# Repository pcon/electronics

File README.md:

# Electronics Projects

This is a home for my various electronic projects.

# Home Monitor
This board is designed to take a WeMos D1 mini and provide traces to a OLED display and a humidity / temperature sensor.

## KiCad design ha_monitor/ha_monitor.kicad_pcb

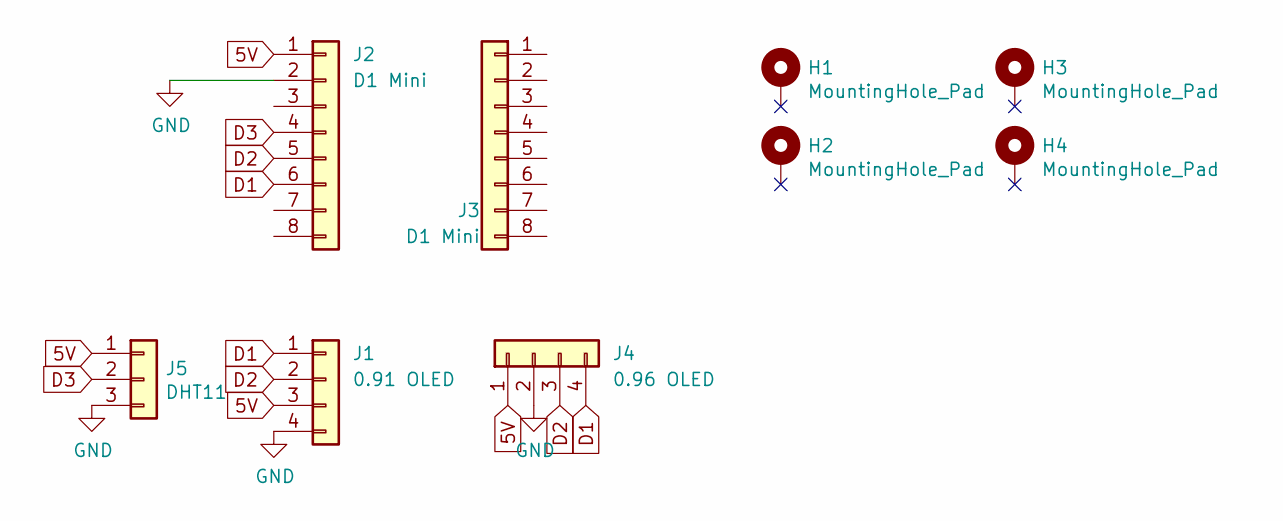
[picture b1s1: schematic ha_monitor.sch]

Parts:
H1, H2, H3, H4: MountingHole_Pad; MountingHole_3.2mm_M3_Pad
J1: 0.91 OLED; PinSocket_1x04_P2.54mm_Vertical
J2, J3: D1 Mini; PinSocket_1x08_P2.54mm_Vertical
J4: 0.96 OLED; PinSocket_1x04_P2.54mm_Vertical
J5: DHT11; PinSocket_1x03_P2.54mm_Vertical

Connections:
5V: J1.3, J2.1, J4.1, J5.1
D1: J1.1, J2.6, J4.4
D2: J1.2, J2.5, J4.3
D3: J2.4, J5.2
GND: J1.4, J2.2, J4.2, J5.3

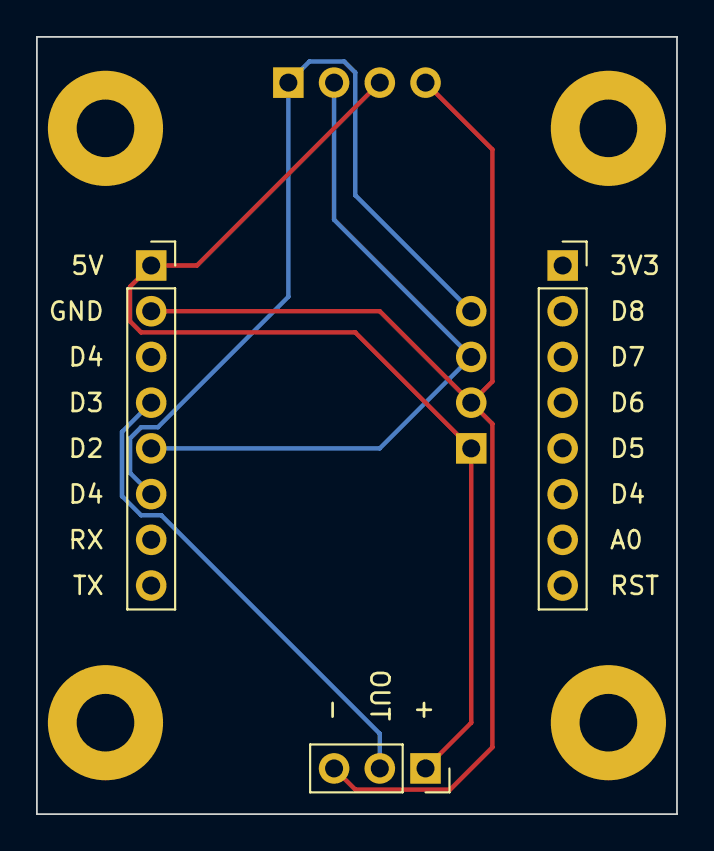
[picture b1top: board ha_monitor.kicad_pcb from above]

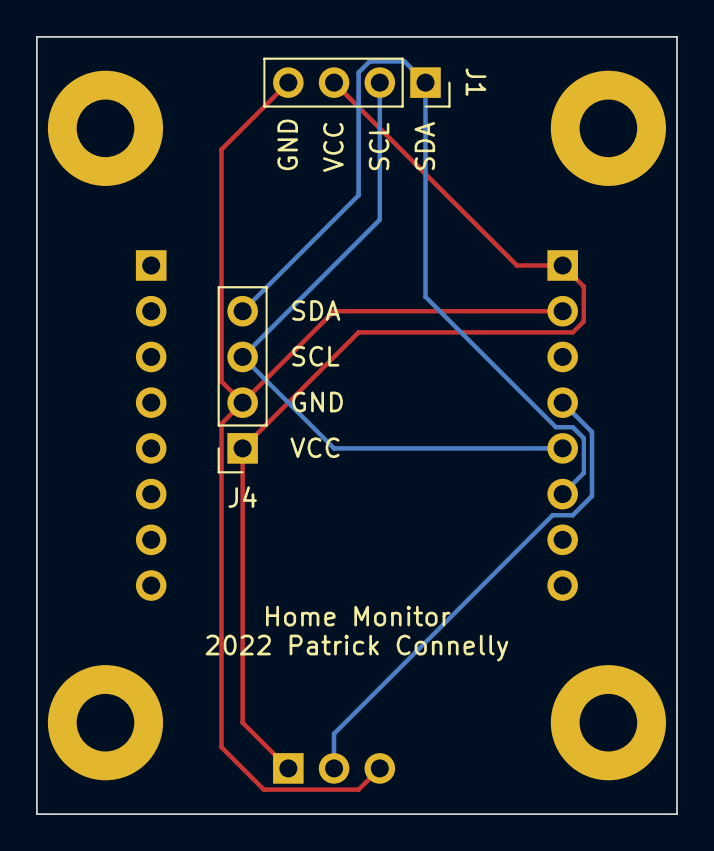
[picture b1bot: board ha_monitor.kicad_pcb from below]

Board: 2 copper layers, 35.6 x 43.2 mm, 9 parts (2 on the bottom side), 5 nets.

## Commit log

2021-11-22 Adding initial design of home assistant monitor
2021-11-22 Fixing bad folder structure
2021-11-22 Removing bad render images
2022-08-09 Adding name silkscreen and plots
2026-02-01 Adding other projects
2026-02-01 Cleaning up
